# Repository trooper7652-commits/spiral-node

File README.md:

# Spiral Node
**Spiral Node: a pocket e-ink device that hands you ideas and leaves the thinking to you. Offline. Open source.**

[Try it in your browser →](https://spiral-node-helix-velocities.vercel.app/try)

## What it is

* **Fully offline**: no internet, no account, nothing leaves the device.
* **E-ink**: a 2.13 inch, 250x122 black-and-white screen.
* **Scripts**: small Python loops that show something to think about every 15, 30 or 60 seconds. Built in: Fun Fact + Question, Quick Story, and Connect (two random topics: what links them?).
* **No repeats**: every entry shown is logged; when a library runs out, you choose to start over.
* **Spiral wheel**: one wheel for up, down, left, right and press.
* **Prototype in progress**: the hardware is being tested. Battery life isn't measured yet.
* **Sourced facts**: every fact links to where it came from.

## Star history

## Quick start
### OS
```
cd os
python -m venv .venv && . .venv/bin/activate
pip install "Pillow>=10.1" pytest
python -m pytest -q
python -m spiral --snapshot out.png
```

### Website
```
cd website
npm install
npm run dev        # http://localhost:3000, the simulator is at /try
npm test
```

## Star the repo and write a script

If Spiral Node sparks something for you, a star helps other people find it. Better still, write a script: copy `scripts/TEMPLATE`, follow [CONTRIBUTING.md](CONTRIBUTING.md), and see your pages on the real Spiral OS in the simulator. Pick up a [good first issue](https://github.com/trooper7652-commits/spiral-node/issues?q=is%3Aissue+is%3Aopen+label%3A%22good+first+issue%22) or say hello in [Discussions](https://github.com/trooper7652-commits/spiral-node/discussions).

## Folders
| Folder | Description |
| :--- | :--- |
| `os/` | Spiral OS, in Python |
| `website/` | The website and the browser simulator |
| `scripts/` | Community scripts, and `TEMPLATE` to start yours |
| `hardware/` | Prototype parts and form factor |
| `docs/` | Images for this README |
| `LICENSES/` | Licence texts and which folder uses which |

## Licences

Code is GPL-3.0 ([LICENSE](LICENSE)). Hardware notes are CERN-OHL-S-2.0. Docs, art and script content are CC BY-SA 4.0. See [LICENSES/README.md](LICENSES/README.md).

Made by Helix Velocities.

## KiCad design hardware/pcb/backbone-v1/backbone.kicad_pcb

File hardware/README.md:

# Hardware

**Prototype in progress. Parts are being tested; nothing here is final.**

## Prototype parts

| Part | Description |
| :--- | :--- |
| Orange Pi Zero 2W | Main processing board |
| E-paper display | 2.13 inch, 250x122 pixels, black and white |
| PiSugar 3 | Power management board |
| Buttons | Seven inputs: five (up, down, left, right, select) that become one spiral wheel, plus Back and Home |
| LiPo battery | 1,800 mAh flat cell |
| Heatsink | Flat stick-on copper |

## Status
* Battery life is not measured yet.
* The LX-LBC3.1 module and exact battery cell are still to be measured.
* There is no enclosure CAD yet.

## Build it
* [build-docs/](build-docs/README.md): parts list with quantities, pin-by-pin wiring, build stages.
* [pcb/backbone-v1/](pcb/backbone-v1/): the button backbone board. KiCad files, the script that draws it, factory files and a 1:1 paper test print.
* [bring-up.md](bring-up.md): set up the board step by step.
* [compatibility-findings.md](compatibility-findings.md): research notes on how the parts fit together, with sources.

## Form factor
See [form-factor.md](form-factor.md) for design details.

## Licence
This hardware design is licensed under CERN-OHL-S-2.0. See [../LICENSES/CERN-OHL-S-2.0.txt](../LICENSES/CERN-OHL-S-2.0.txt).

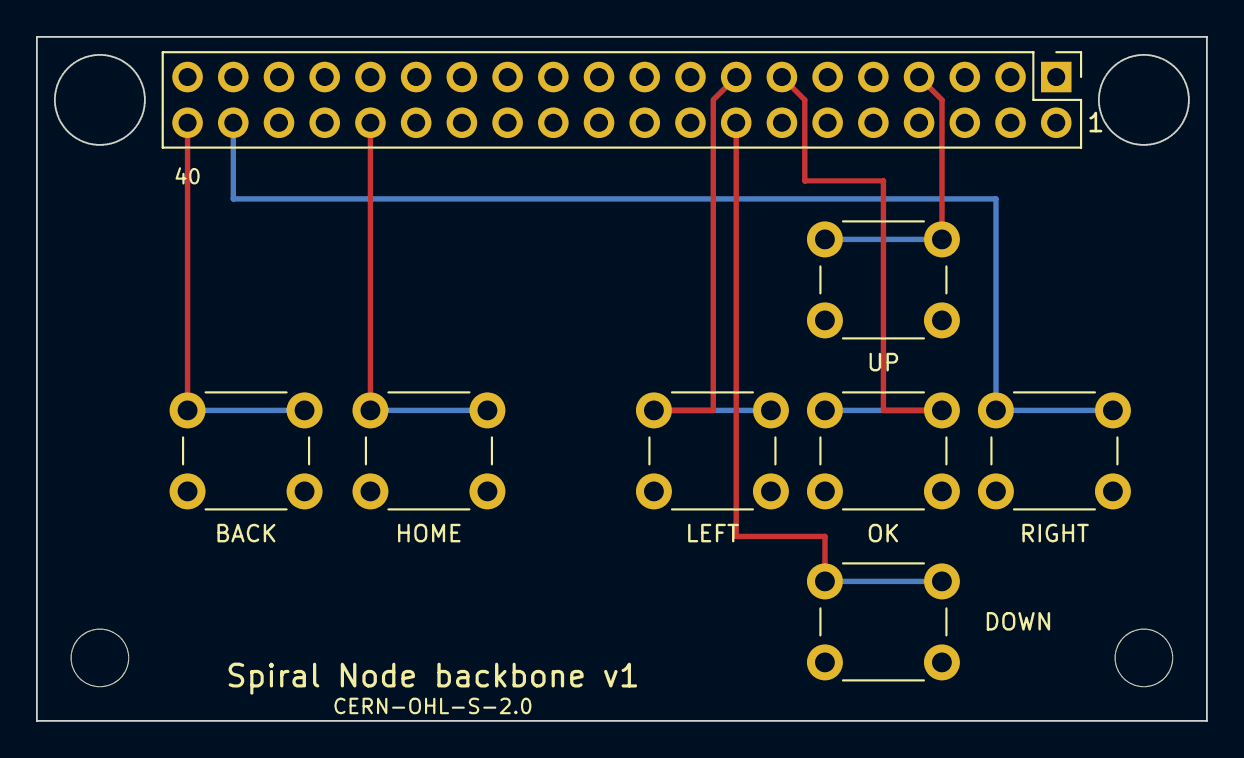
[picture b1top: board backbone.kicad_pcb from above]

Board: 2 copper layers, 65.0 x 38.0 mm, 10 parts (0 on the bottom side), 8 nets.

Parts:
H1, H2: MountingHole_3.2mm_M3
J1: PinHeader_2x20_P2.54mm_Vertical
SW1, SW2, SW3, SW4, SW5, SW6, SW7: SW_PUSH_6mm_H5mm

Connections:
BTN_BACK: J1.40, SW6.1
BTN_DOWN: J1.16, SW2.1
BTN_HOME: J1.32, SW7.1
BTN_LEFT: J1.15, SW3.1
BTN_RIGHT: J1.38, SW4.1
BTN_SELECT: J1.13, SW5.1
BTN_UP: J1.7, SW1.1
GND: J1.6, J1.9, J1.14, J1.20, J1.25, J1.30, J1.34, J1.39, SW1.2, SW2.2, SW3.2, SW4.2, SW5.2, SW6.2, SW7.2
